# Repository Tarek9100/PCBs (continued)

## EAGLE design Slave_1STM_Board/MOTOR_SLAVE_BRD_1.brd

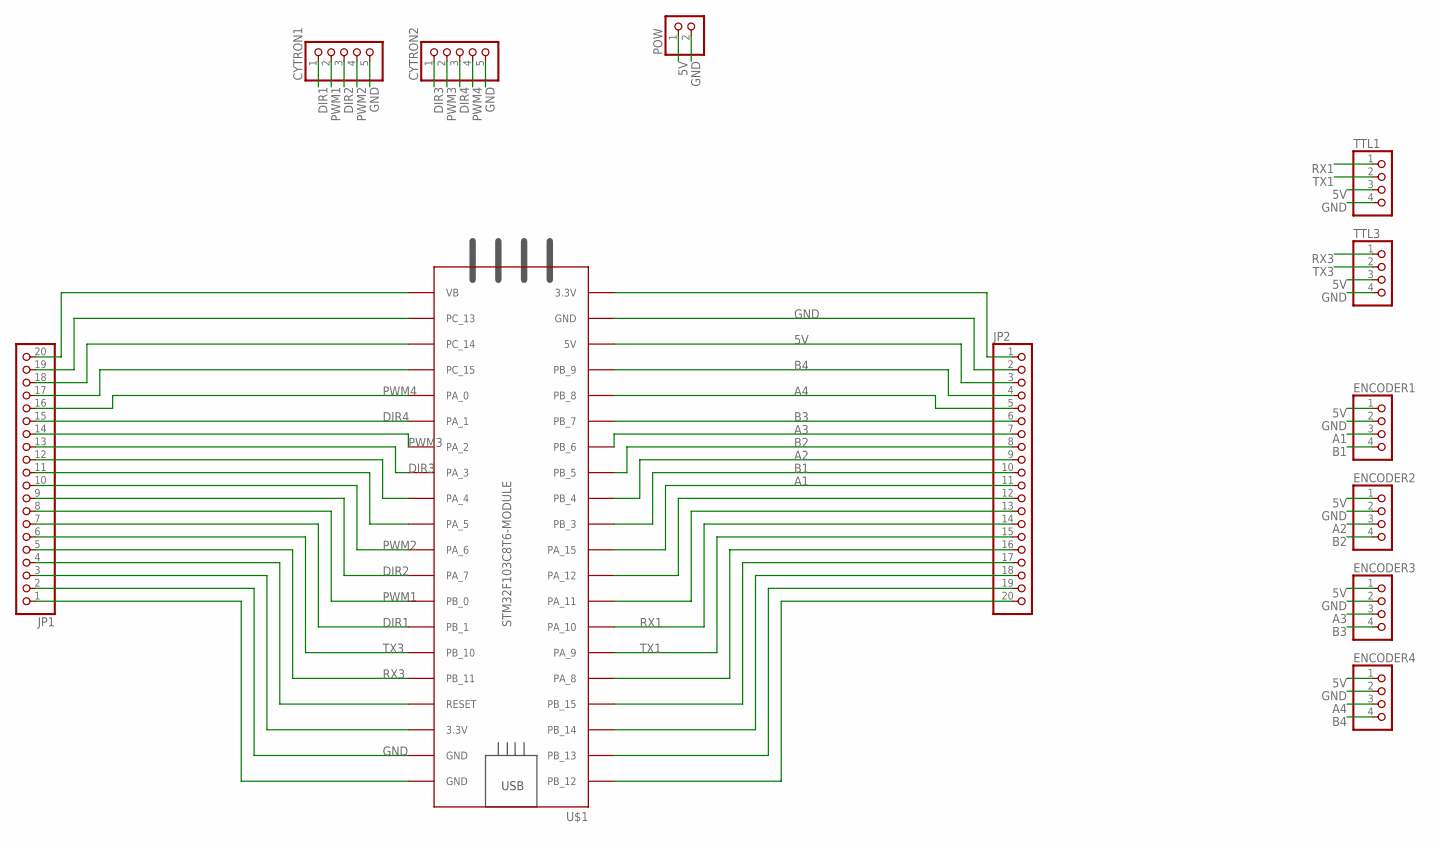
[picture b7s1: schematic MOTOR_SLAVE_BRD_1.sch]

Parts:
CYTRON1, CYTRON2: PINHD-5_DATA; 1X05_DATA
ENCODER1, ENCODER2, ENCODER3, ENCODER4: PINHD-4_DATA; 1X04_DATA
JP1, JP2: PINHD-1X20; 1X20
POW: PINHD-2_DATA; 1X02_DATA
TTL1, TTL3: PINHD-4_DATA; 1X04_DATA
U$1: STM32F103C8T6-MODULE

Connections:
5V: ENCODER1.1, ENCODER2.1, ENCODER3.1, ENCODER4.1, JP2.3, POW.1, TTL1.3, TTL3.3, U$1.5V
A1: ENCODER1.3, JP2.11, U$1.PA_15
A2: ENCODER2.3, JP2.9, U$1.PB_4
A3: ENCODER3.3, JP2.7, U$1.PB_6
A4: ENCODER4.3, JP2.5, U$1.PB_8
B1: ENCODER1.4, JP2.10, U$1.PB_3
B2: ENCODER2.4, JP2.8, U$1.PB_5
B3: ENCODER3.4, JP2.6, U$1.PB_7
B4: ENCODER4.4, JP2.4, U$1.PB_9
DIR1: CYTRON1.1, JP1.7, U$1.PB_1
DIR2: CYTRON1.3, JP1.9, U$1.PA_7
DIR3: CYTRON2.1, JP1.13, U$1.PA_3
DIR4: CYTRON2.3, JP1.15, U$1.PA_1
GND: CYTRON1.5, CYTRON2.5, ENCODER1.2, ENCODER2.2, ENCODER3.2, ENCODER4.2, JP1.2, JP2.2, POW.2, TTL1.4, TTL3.4, U$1.GND_1 (GND), U$1.GND_2 (GND)
unnamed: JP1.20, U$1.VB
unnamed: JP1.19, U$1.PC_13
unnamed: JP1.18, U$1.PC_14
unnamed: JP1.17, U$1.PC_15
unnamed: JP1.12, U$1.PA_4
unnamed: JP1.11, U$1.PA_5
unnamed: JP1.4, U$1.RESET
unnamed: JP1.3, U$1.3.3V_2 (3.3V)
unnamed: JP1.1, U$1.GND_3 (GND)
unnamed: JP2.1, U$1.3.3V_1 (3.3V)
unnamed: JP2.12, U$1.PA_12
unnamed: JP2.13, U$1.PA_11
unnamed: JP2.16, U$1.PA_8
unnamed: JP2.17, U$1.PB_15
unnamed: JP2.18, U$1.PB_14
unnamed: JP2.19, U$1.PB_13
unnamed: JP2.20, U$1.PB_12
PWM1: CYTRON1.2, JP1.8, U$1.PB_0
PWM2: CYTRON1.4, JP1.10, U$1.PA_6
PWM3: CYTRON2.2, JP1.14, U$1.PA_2
PWM4: CYTRON2.4, JP1.16, U$1.PA_0
RX1: JP2.14, TTL1.1, U$1.PA_10
RX3: JP1.5, TTL3.1, U$1.PB_11
TX1: JP2.15, TTL1.2, U$1.PA_9
TX3: JP1.6, TTL3.2, U$1.PB_10

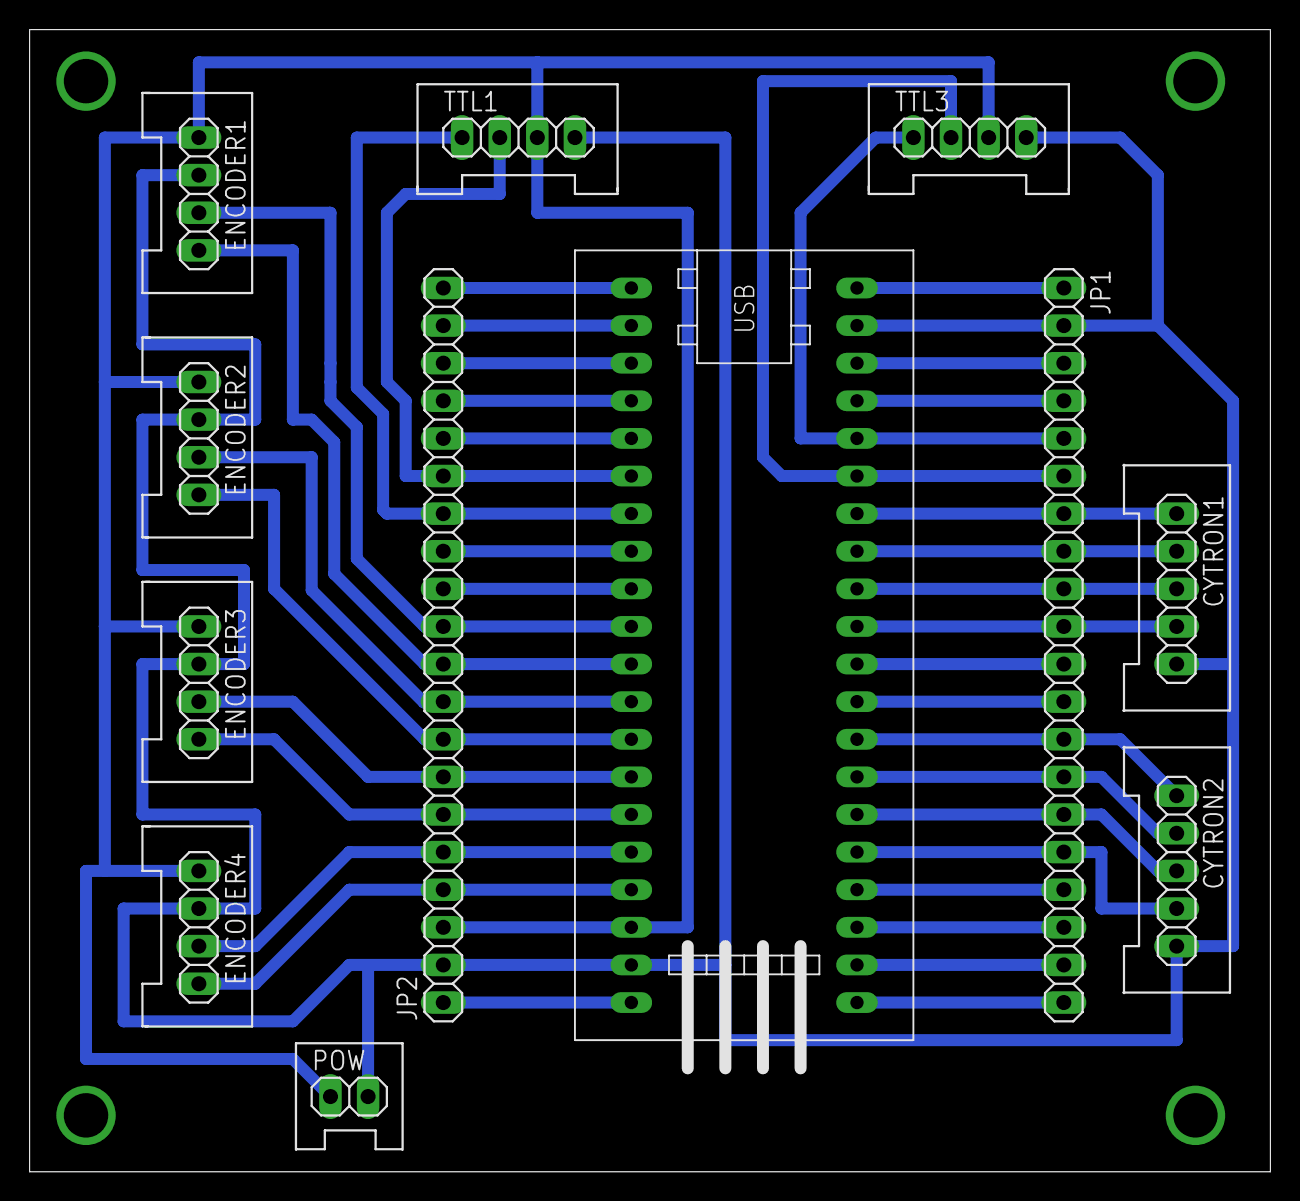
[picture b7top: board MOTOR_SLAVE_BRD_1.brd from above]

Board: 2 copper layers, 83.8 x 77.1 mm, 12 parts (0 on the bottom side), 39 nets.
